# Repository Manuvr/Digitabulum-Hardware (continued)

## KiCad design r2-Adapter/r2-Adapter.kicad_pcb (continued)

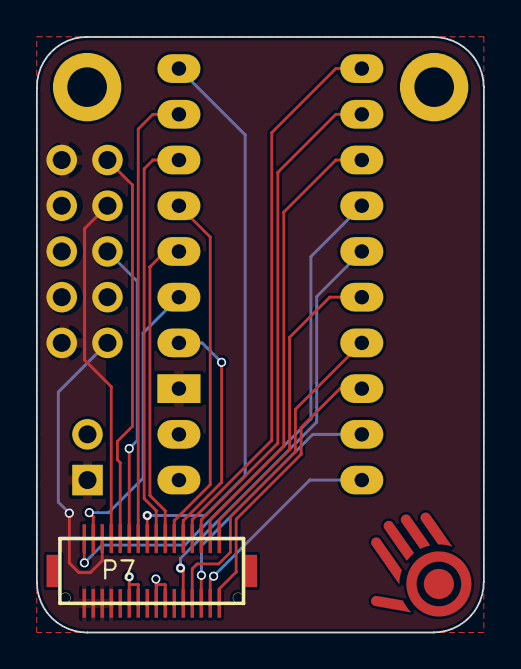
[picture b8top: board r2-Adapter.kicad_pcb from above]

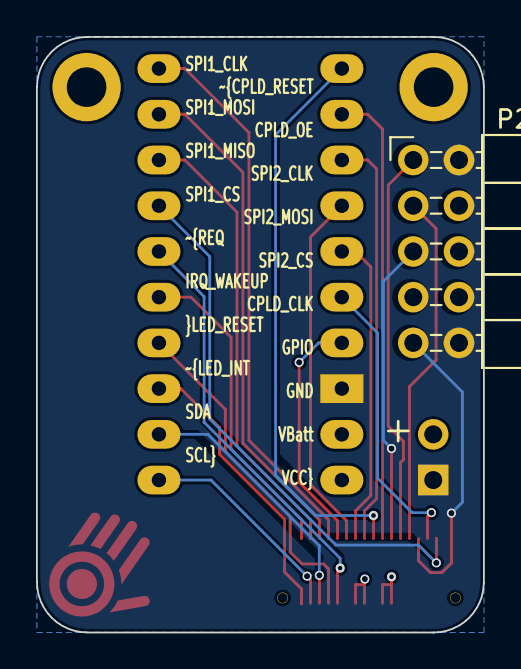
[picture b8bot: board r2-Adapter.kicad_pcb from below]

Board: 4 copper layers, 24.8 x 33.1 mm, 7 parts (2 on the bottom side), 24 nets.

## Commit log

2017-06-17 Tweaks to library relationships.
2017-06-17 Adding in some modules.
2017-06-17 Doc tweak.
2017-06-17 More hardware publishing stuff.
2017-06-19 Set theme jekyll-theme-slate
2017-06-20 Compute-WROOM32/
2017-06-20 Adding Compute-WROOM32
2017-06-20 Removing stray yml file.
2017-06-20 Adding modules.
2017-06-20 Adding datasheets.
2017-06-20 Readme tweaks.
2017-07-05 Silkscreen fix.
2017-08-22 Fixed silkscreen mistake.
2017-09-08 Filling in BOM.
2017-09-08 Adding backplane PCB project, despite incomplete BOM.
2017-09-09 BOM filled out, but board not verified.
2017-09-09 BOM completion.
2017-09-09 Minor change to BOM script.
2017-09-09 Repo meta commit.
2017-10-04 Adding small tools catch-all project.
2017-10-25 Adding dev kit hardware.
2017-10-28 Adding BOM info.
2017-11-08 Documentation update.
2018-02-26 Fixed some bugs in the Dev Harness.
2018-02-26 Doc update and path shuffle, step 1.
2018-02-26 Doc update and path shuffle, step 2.
2018-12-30 Updated compute module to fix a bug, and to use the WROOM32-U.
2018-12-30 Updating to r2 backplane fixes from last year.
2018-12-30 Removing autorouter cruft.
2019-02-10 Compute module will now take either WROOM32 module.
